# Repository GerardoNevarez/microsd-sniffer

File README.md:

# MicroSD Sniffer

Based on [*SparkFun microSD Sniffer (TOL-09419)*](https://www.sparkfun.com/products/9419)
GitHub Repo: [https://github.com/sparkfun/MicroSD_Sniffer](https://github.com/sparkfun/MicroSD_Sniffer)

Updated uSD socket with [XUNPU TF-115-BCP9 - LCSC Part# C720505](https://www.lcsc.com/product-detail/SD-Card-Connectors_XUNPU-TF-115-BCP9_C720505.html)

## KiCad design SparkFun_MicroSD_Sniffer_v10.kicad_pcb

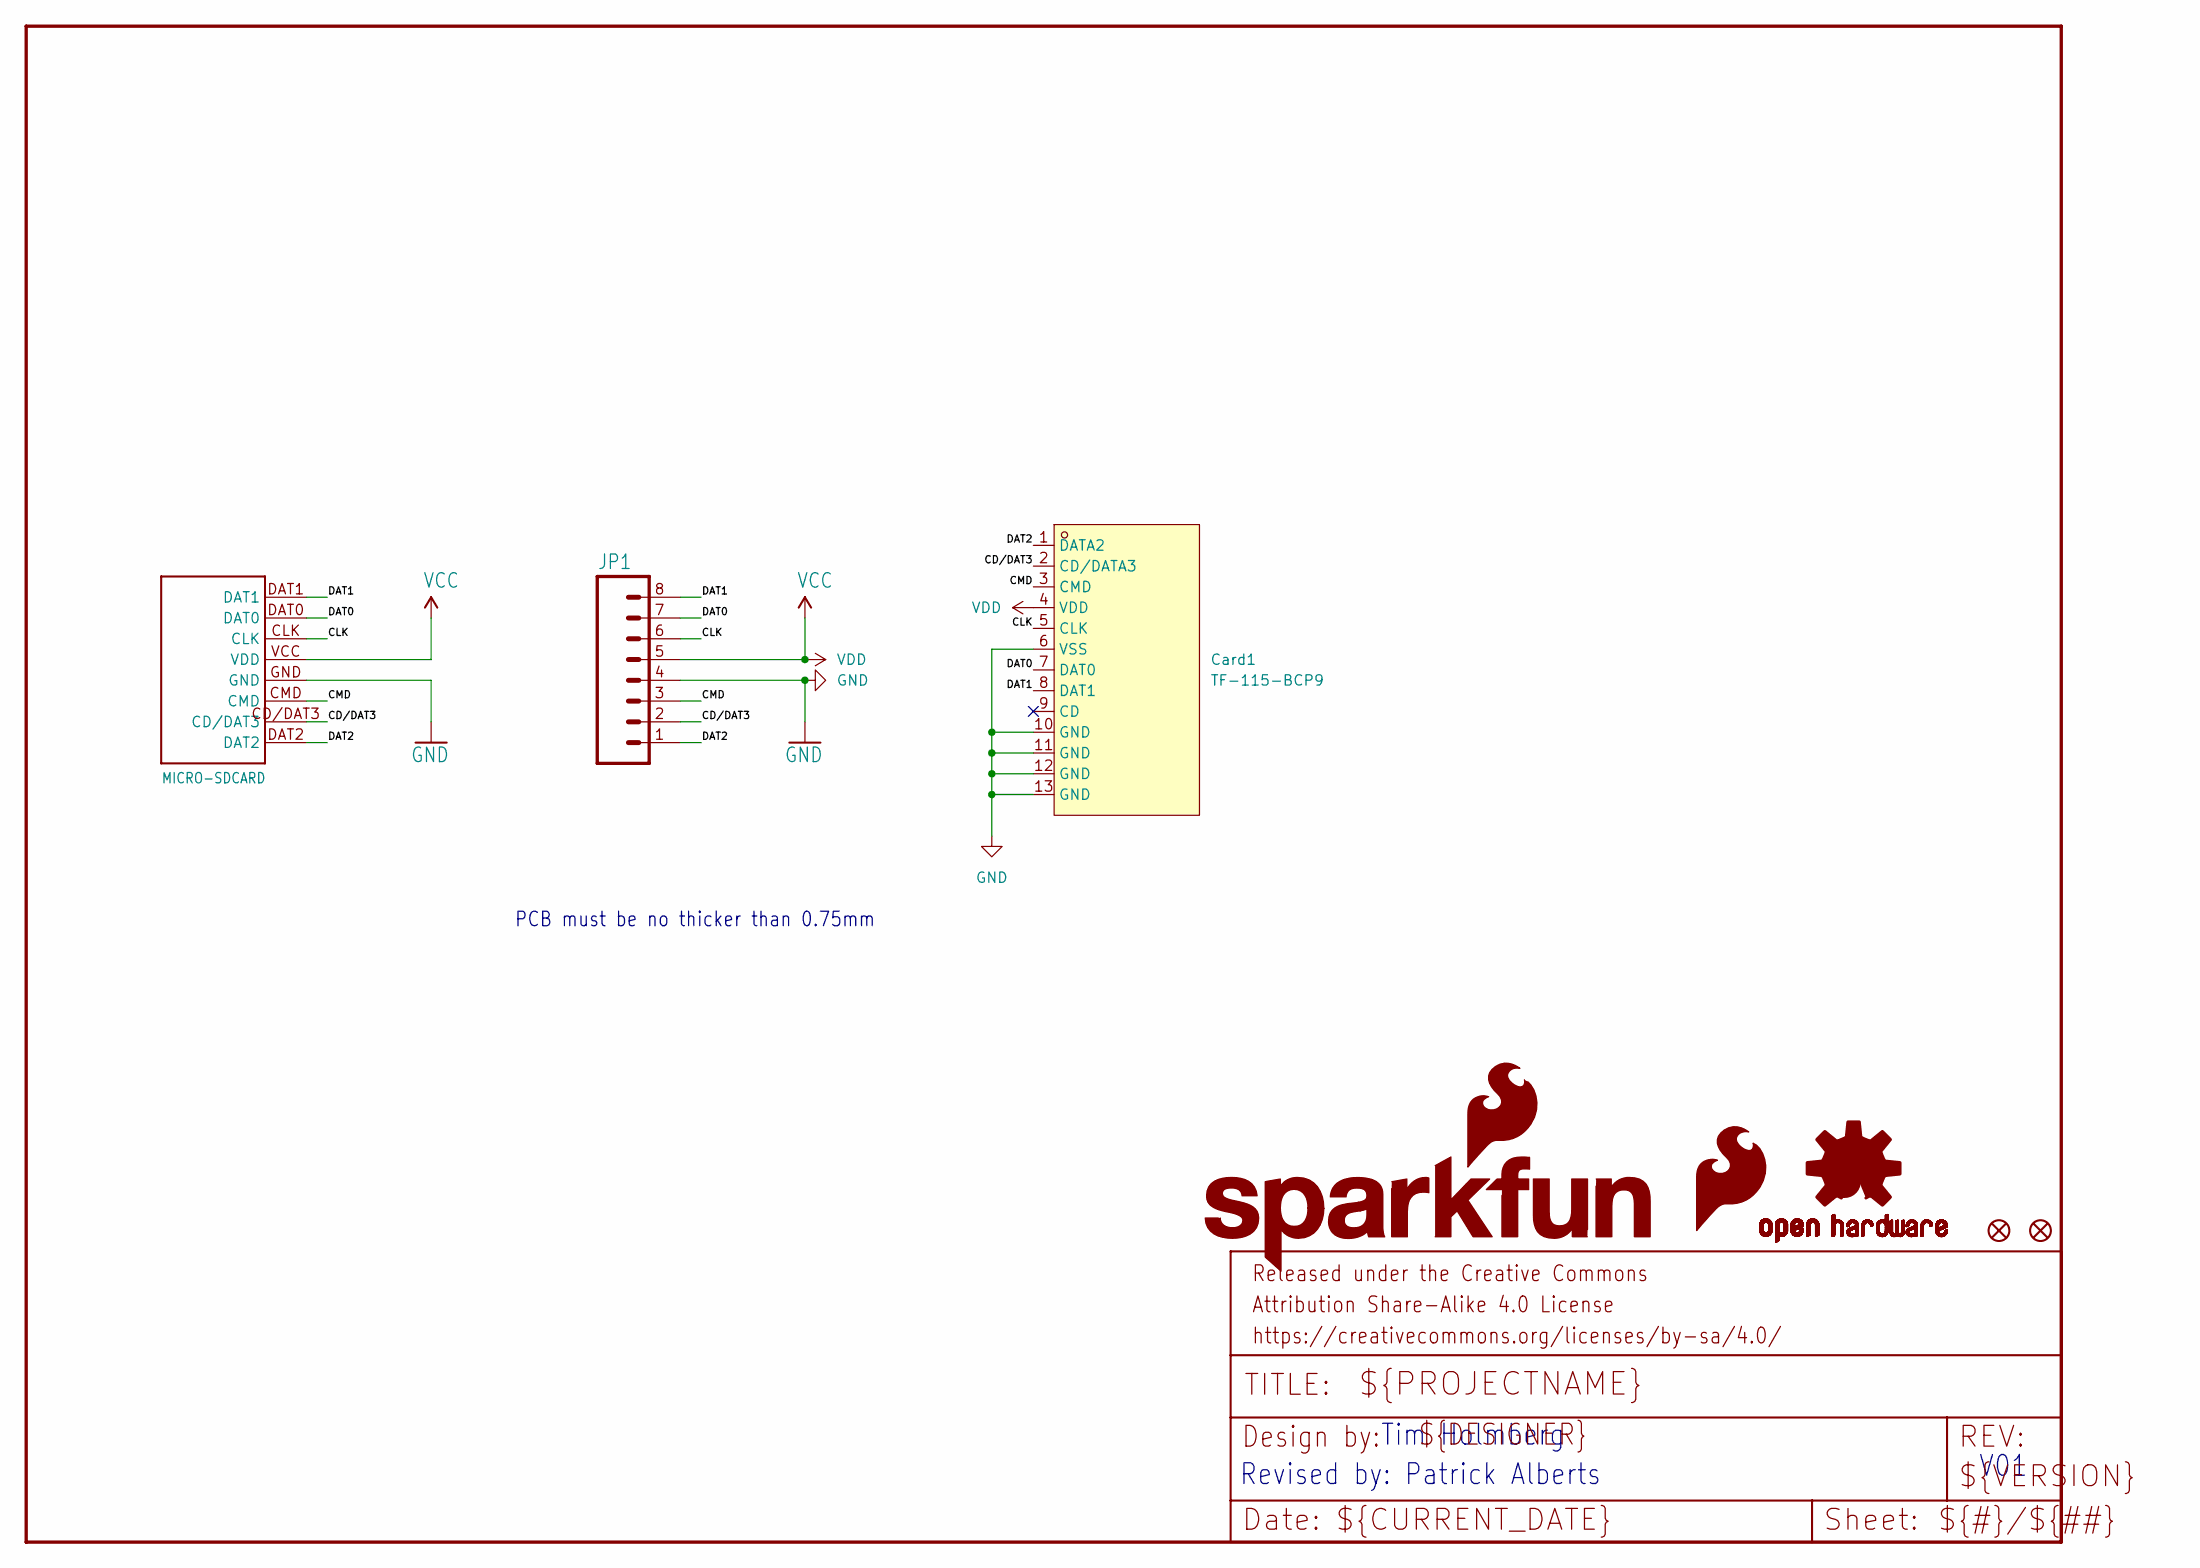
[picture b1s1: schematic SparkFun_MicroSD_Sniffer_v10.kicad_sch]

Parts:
Card1: TF-115-BCP9; TF-SMD_TF-115-BCP9; LCSC Part C720505
FID1, FID2: FIDUCIAL1X2; FIDUCIAL-1X2
FRAME1: FRAME-LETTER; CREATIVE_COMMONS
JP1: M08; 1X08
LOGO1: OSHW-LOGOM; OSHW-LOGO-M
LOGO2: SFE_LOGO_FLAME.2_INCH; SFE_LOGO_FLAME_.2
LOGO3: SFE_LOGO_NAME_FLAME.1_INCH; SFE_LOGO_NAME_FLAME_.1
U1: MICRO-SDCARD

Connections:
/CD/DAT3: Card1.2 (CD/DATA3), JP1.2, U1.CD/DAT3
/CLK: Card1.5 (CLK), JP1.6, U1.CLK
/CMD: Card1.3 (CMD), JP1.3, U1.CMD
/DAT0: Card1.7 (DAT0), JP1.7, U1.DAT0
/DAT1: Card1.8 (DAT1), JP1.8, U1.DAT1
/DAT2: Card1.1 (DATA2), JP1.1, U1.DAT2
GND: Card1.6 (VSS), Card1.10 (GND), Card1.11 (GND), Card1.12 (GND), Card1.13 (GND), JP1.4, U1.GND
VCC: Card1.4 (VDD), JP1.5, U1.VCC (VDD)

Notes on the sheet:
Revised by: Patrick Alberts
V01
PCB must be no thicker than 0.75mm
Tim Holmberg

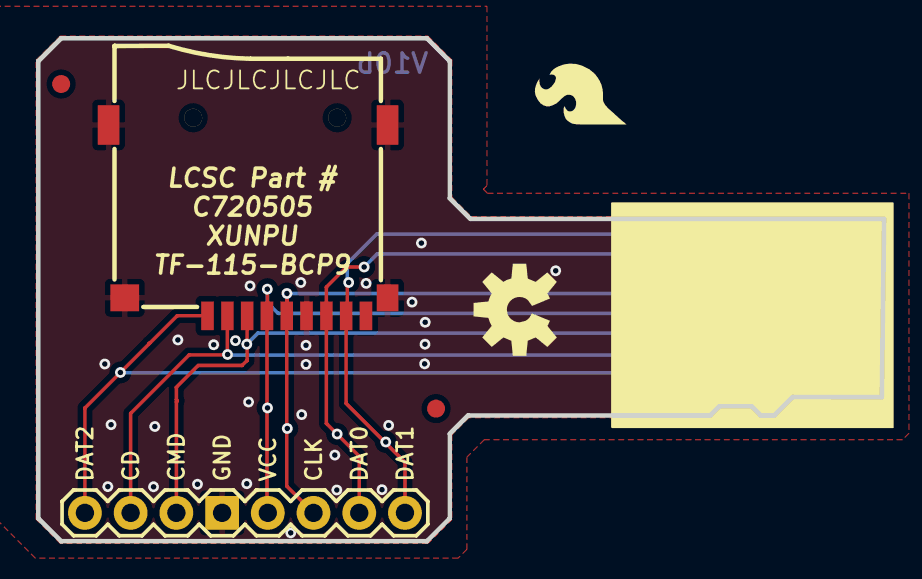
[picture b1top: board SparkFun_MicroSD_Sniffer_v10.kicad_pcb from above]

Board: 16 copper layers, 47.0 x 27.9 mm, 9 parts (1 on the bottom side), 8 nets.

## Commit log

2023-12-03 Add silkscreen to increase height in the uSD section

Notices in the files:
SparkFun_MicroSD_Sniffer_v10.kicad_sch:
https://creativecommons.org/licenses/by-sa/4.0
Released under the Creative Commons
parts and their libraries:
Released under the Creative Commons Attribution Share-Alike 4.0 License
